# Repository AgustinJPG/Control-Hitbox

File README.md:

En este github tengo todos los archivos de mi proyecto de control hitbox en donde trabaje el codigo
con la libreria keyboard.h, ademas de trabajar el esquematico y el pcb de la placa.
Mas detalles e informacion en el pdf.

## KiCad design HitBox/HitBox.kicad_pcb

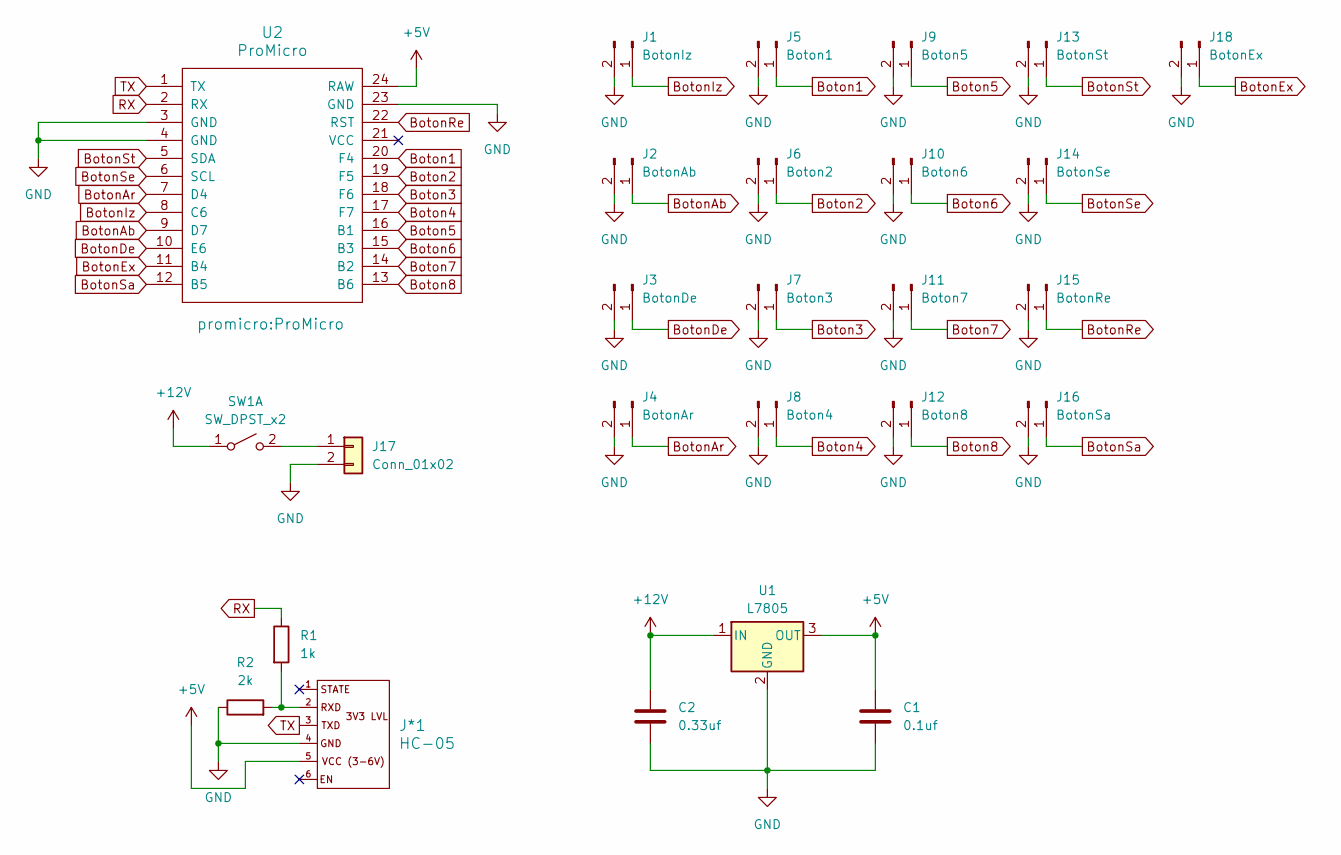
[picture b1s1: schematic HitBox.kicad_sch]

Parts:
C1: 0.1uf; C_0805_2012Metric
C2: 0.33uf; C_0805_2012Metric
J1: BotonIz; PinHeader_1x02_P2.54mm_Vertical
J2: BotonAb; PinHeader_1x02_P2.54mm_Vertical
J3: BotonDe; PinHeader_1x02_P2.54mm_Vertical
J4: BotonAr; PinHeader_1x02_P2.54mm_Vertical
J5: Boton1; PinHeader_1x02_P2.54mm_Vertical
J6: Boton2; PinHeader_1x02_P2.54mm_Vertical
J7: Boton3; PinHeader_1x02_P2.54mm_Vertical
J8: Boton4; PinHeader_1x02_P2.54mm_Vertical
J9: Boton5; PinHeader_1x02_P2.54mm_Vertical
J10: Boton6; PinHeader_1x02_P2.54mm_Vertical
J11: Boton7; PinHeader_1x02_P2.54mm_Vertical
J12: Boton8; PinHeader_1x02_P2.54mm_Vertical
J13: BotonSt; PinHeader_1x02_P2.54mm_Vertical
J14: BotonSe; PinHeader_1x02_P2.54mm_Vertical
J15: BotonRe; PinHeader_1x02_P2.54mm_Vertical
J16: BotonSa; PinHeader_1x02_P2.54mm_Vertical
J17: Conn_01x02; TerminalBlock_MaiXu_MX126-5.0-02P_1x02_P5.00mm
J18: BotonEx; PinHeader_1x02_P2.54mm_Vertical
J*1: HC-05
R1: 1k; C_0805
R2: 2k; C_0805
SW1: SW_DPST_x2; SW_PUSH_1P1T_6x3.5mm_H5.0_APEM_MJTP1250
U1: L7805; TO-263-3_TabPin2
U2: ProMicro

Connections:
+5V: C1.1, J*1.5, U1.3 (OUT), U2.24 (RAW)
+12V: C2.1, SW1.1 (A), U1.1 (IN)
Boton1: J5.1, U2.20 (F4)
Boton2: J6.1, U2.19 (F5)
Boton3: J7.1, U2.18 (F6)
Boton4: J8.1, U2.17 (F7)
Boton5: J9.1, U2.16 (B1)
Boton6: J10.1, U2.15 (B3)
Boton7: J11.1, U2.14 (B2)
Boton8: J12.1, U2.13 (B6)
BotonAb: J2.1, U2.9 (D7)
BotonAr: J4.1, U2.7 (D4)
BotonDe: J3.1, U2.10 (E6)
BotonEx: J18.1, U2.11 (B4)
BotonIz: J1.1, U2.8 (C6)
BotonRe: J15.1, U2.22 (RST)
BotonSa: J16.1, U2.12 (B5)
BotonSe: J14.1, U2.6 (SCL)
BotonSt: J13.1, U2.5 (SDA)
GND: C1.2, C2.2, J1.2, J2.2, J3.2, J4.2, J5.2, J6.2, J7.2, J8.2, J9.2, J10.2, J11.2, J12.2, J13.2, J14.2, J15.2, J16.2, J17.2, J18.2, J*1.4, R2.1, U1.2 (GND), U2.3 (GND), U2.4 (GND), U2.23 (GND)
unnamed: J17.1, SW1.2 (B)
unnamed: J*1.2, R1.2, R2.2
RX: R1.1, U2.2 (RX)
TX: J*1.3, U2.1 (TX)

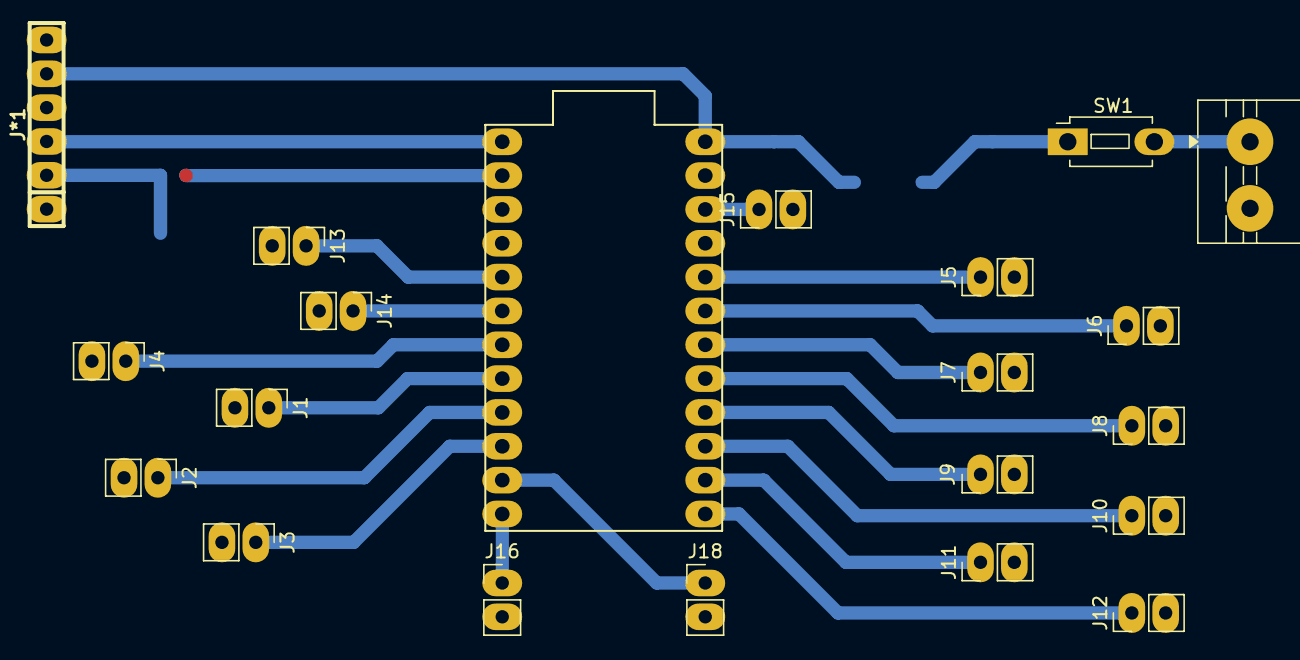
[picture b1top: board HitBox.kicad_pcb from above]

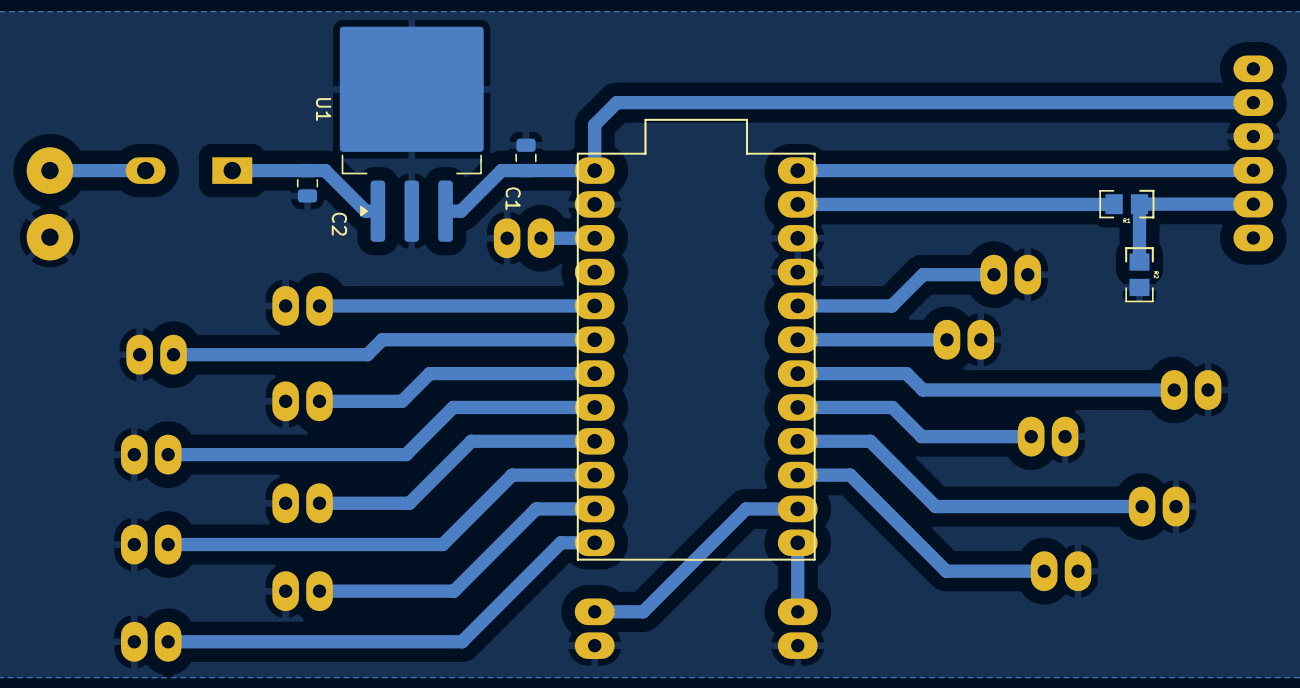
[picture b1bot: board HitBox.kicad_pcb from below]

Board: 2 copper layers, 26 parts (5 on the bottom side), 24 nets.

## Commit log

2025-11-30 La Hitbox
2025-11-30 Control-Hitbox
2025-11-30 README.md
